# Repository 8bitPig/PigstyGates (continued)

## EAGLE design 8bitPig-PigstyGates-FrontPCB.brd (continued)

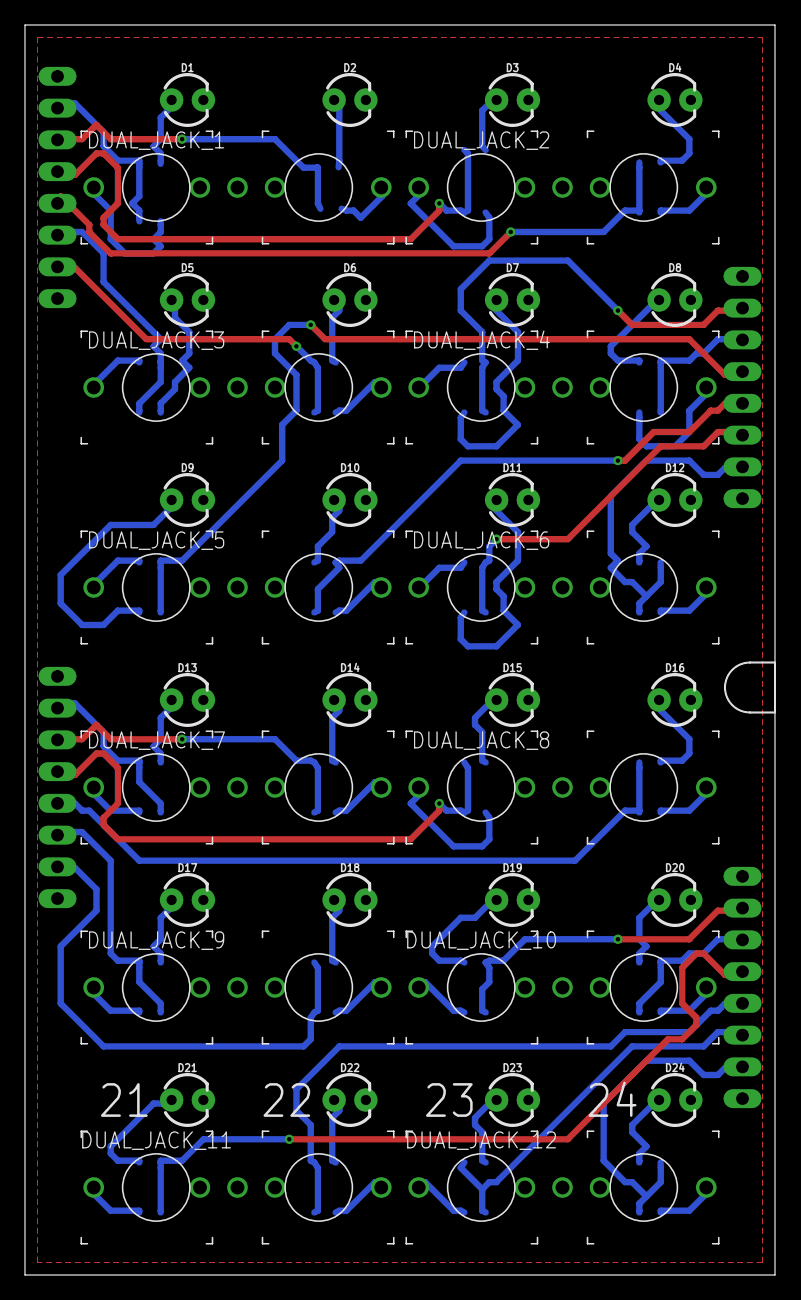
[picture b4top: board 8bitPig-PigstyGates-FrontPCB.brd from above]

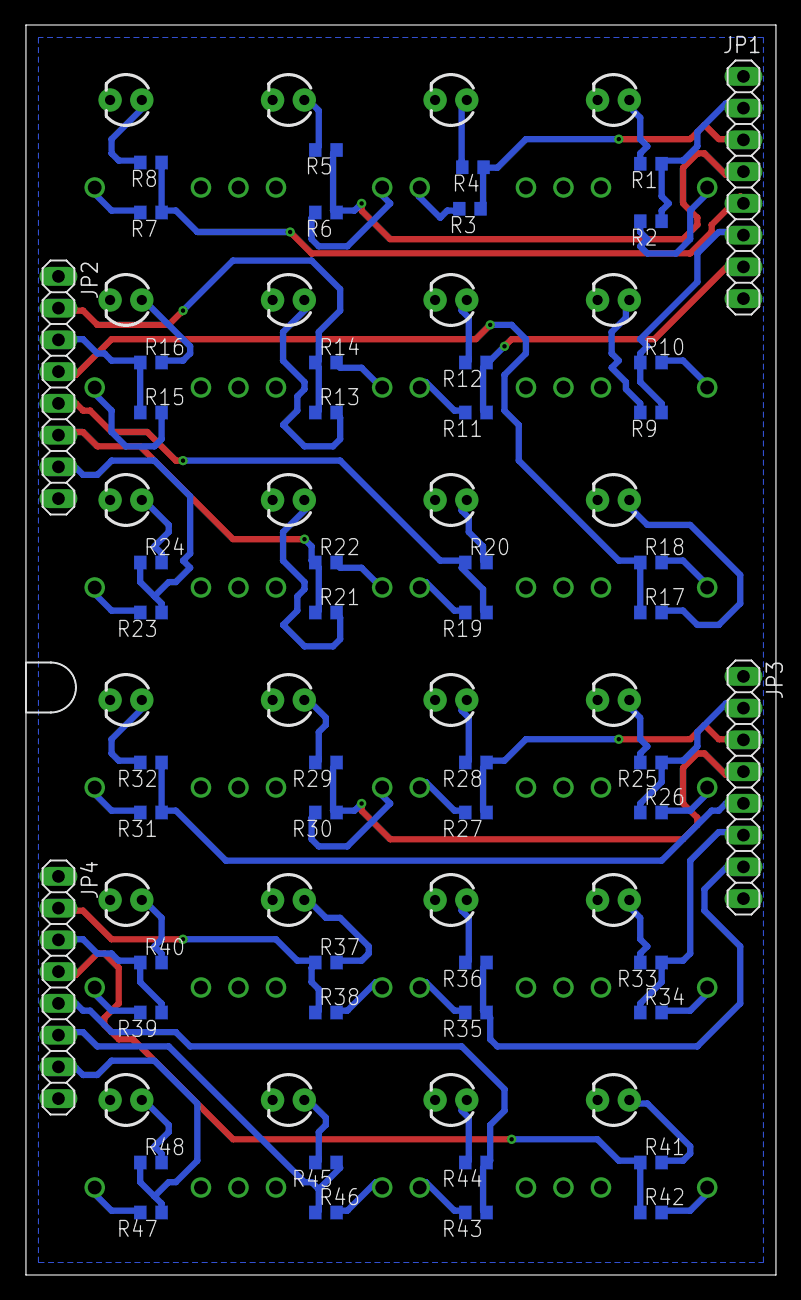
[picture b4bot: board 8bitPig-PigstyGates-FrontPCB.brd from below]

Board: 2 copper layers, 59.9 x 99.8 mm, 89 parts (52 on the bottom side), 73 nets.

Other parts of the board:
U$1: PANEL_CABLE_CUTOUT

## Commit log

2019-08-19 uploaded v2
    better layout
    better parts. (swapped TL074 for LM324 to drive Gates and LEDs)
    got rid of SPI and connected all 24 Gates to GPIO Pins of the teensy.
    brd still compatible to all teensy small footprint boards. (only the 24 outside PINs used + GND & VIN)
2019-09-25 Add files via upload
    uploaded working hex and ino file
    ino should work for following teensy boards:
    LC, 2.0, 3.0, 3.1, 3.2, 4.0
    (but 4.0 did not work yet because I was not able to select USB-Midi for the Teensy 4.0 boards atm.
    Guess this will be fixed in a future update of Arduino or Teensyduino Software)
